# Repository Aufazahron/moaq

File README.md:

# 🛠️ Sensor Enclosure & Mechanical Components (Casing)

This repository contains a collection of 3D-printable enclosures and mechanical components designed for various sensor modules and mechanical systems. These parts were developed using **PTC Creo Parametric**.

## 📁 Project Structure

The project is organized into three main modules:

### 1. 🌊 Turbidity Sensor Enclosure (`/Turbidity`)
Designed to house and protect turbidity sensors used in water quality monitoring.
*   **Key Features:** Threaded assembly (ulir) for secure fit, sensor mounting base, and protective cover.
*   **Files:** Includes `.stl` for 3D printing and `.prt`/`.asm` for CAD modification.
*   **Visuals:**

### 2. 📏 Ultrasonic Sensor Casing (`/Ultrasonic_Casing`)
A custom mount and enclosure for HC-SR04 type ultrasonic sensors.
*   **Key Features:** Dual-bore front for sensor transducers, compact form factor, and mounting rails.
*   **Files:** `.stl` and `.prt`.
*   **Visuals:**

### 3. 🧪 Stirrer Handle (`/Gagang_Pengaduk`)
Mechanical component for manual or automated stirring systems.
*   **Key Features:** Ergonomic design/compatible connector for stirring rods.
*   **Files:** `.stl` and `.prt`.
*   **Visuals:**

## 🚀 Getting Started

### Prerequisites
*   **For Printing:** Any 3D slicer (Cura, PrusaSlicer, etc.) and a 3D printer.
*   **For Modification:** PTC Creo Parametric (Educational Edition or Professional).

### Installation / Usage
1.  Clone this repository to your local machine.
2.  Navigate to the desired folder.
3.  Use the `.stl` files directly for 3D printing.
4.  Use the `.prt` or `.asm` files if you need to adjust dimensions or features.

## 🛠️ Built With
*   **PTC Creo Parametric** - CAD Software used for modeling.
*   **STL Format** - Ready for 3D Printing.

---
*Developed for sensor integration and mechanical prototyping.*

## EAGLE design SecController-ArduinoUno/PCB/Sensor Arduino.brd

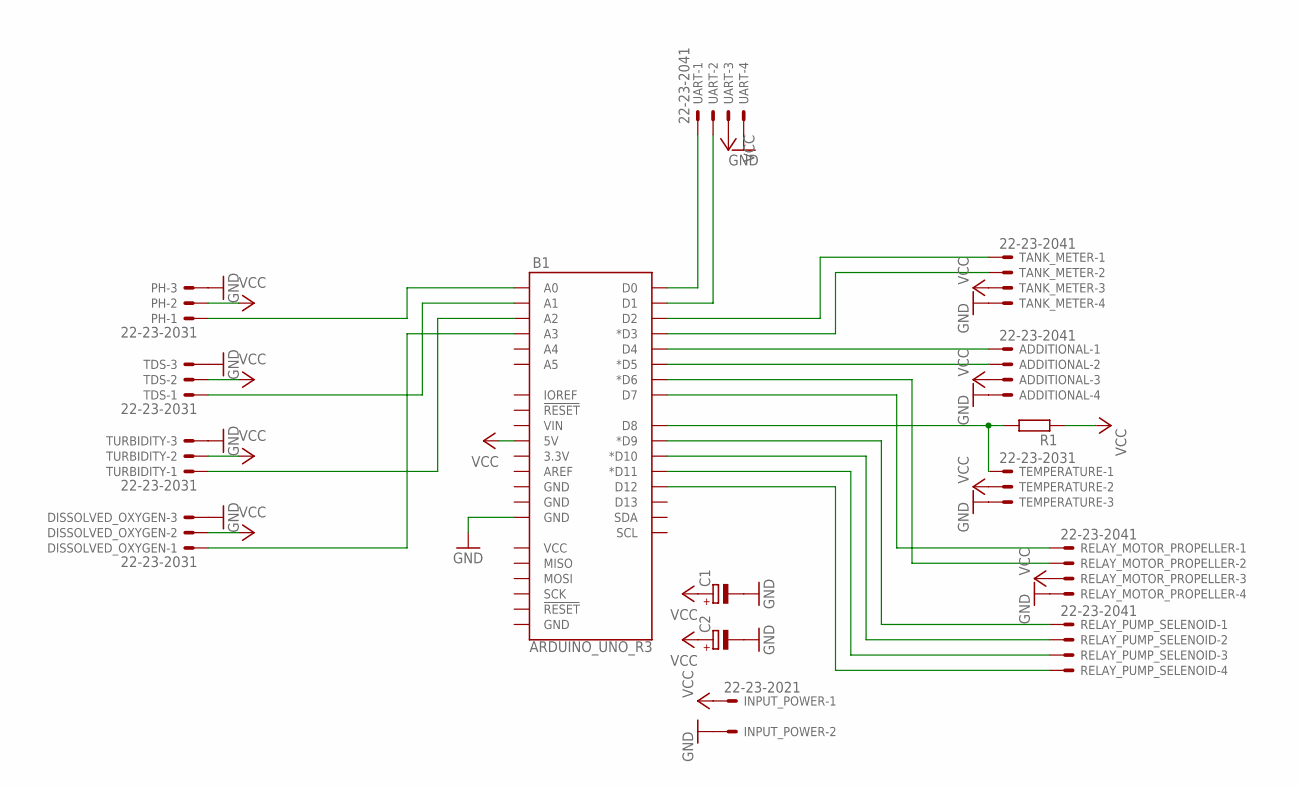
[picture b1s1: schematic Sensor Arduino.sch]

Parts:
ADDITIONAL: 22-23-2041
B1: ARDUINO_UNO_R3; ARDUINO_R3
C1: CPOL-EUE5-10.5; E5-10,5
C2: CPOL-EUE5-6; E5-6
DISSOLVED_OXYGEN: 22-23-2031
INPUT_POWER: 22-23-2021
PH: 22-23-2031
R1: R-EU_0207/12; 0207/12
RELAY_MOTOR_PROPELLER: 22-23-2041
RELAY_PUMP_SELENOID: 22-23-2041
TANK_METER: 22-23-2041
TDS: 22-23-2031
TEMPERATURE: 22-23-2031
TURBIDITY: 22-23-2031
UART: 22-23-2041

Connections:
GND: ADDITIONAL.4, B1.GND@2 (GND), C1.-, C2.-, DISSOLVED_OXYGEN.3, INPUT_POWER.2, PH.3, RELAY_MOTOR_PROPELLER.4, TANK_METER.4, TDS.3, TEMPERATURE.3, TURBIDITY.3, UART.4
unnamed: B1.A0, PH.1
unnamed: B1.A1, TDS.1
unnamed: B1.A2, TURBIDITY.1
unnamed: B1.A3, DISSOLVED_OXYGEN.1
unnamed: B1.D2, TANK_METER.1
unnamed: B1.D3 (*D3), TANK_METER.2
unnamed: ADDITIONAL.1, B1.D4
unnamed: ADDITIONAL.2, B1.D5 (*D5)
unnamed: B1.D8, R1.2, TEMPERATURE.1
unnamed: B1.D6 (*D6), RELAY_MOTOR_PROPELLER.2
unnamed: B1.D7, RELAY_MOTOR_PROPELLER.1
unnamed: B1.D9 (*D9), RELAY_PUMP_SELENOID.1
unnamed: B1.D10 (*D10), RELAY_PUMP_SELENOID.2
unnamed: B1.D11 (*D11), RELAY_PUMP_SELENOID.3
unnamed: B1.D12, RELAY_PUMP_SELENOID.4
unnamed: B1.D1, UART.2
unnamed: B1.D0, UART.1
VCC: ADDITIONAL.3, B1.5V, C1.+, C2.+, DISSOLVED_OXYGEN.2, INPUT_POWER.1, PH.2, R1.1, RELAY_MOTOR_PROPELLER.3, TANK_METER.3, TDS.2, TEMPERATURE.2, TURBIDITY.2, UART.3

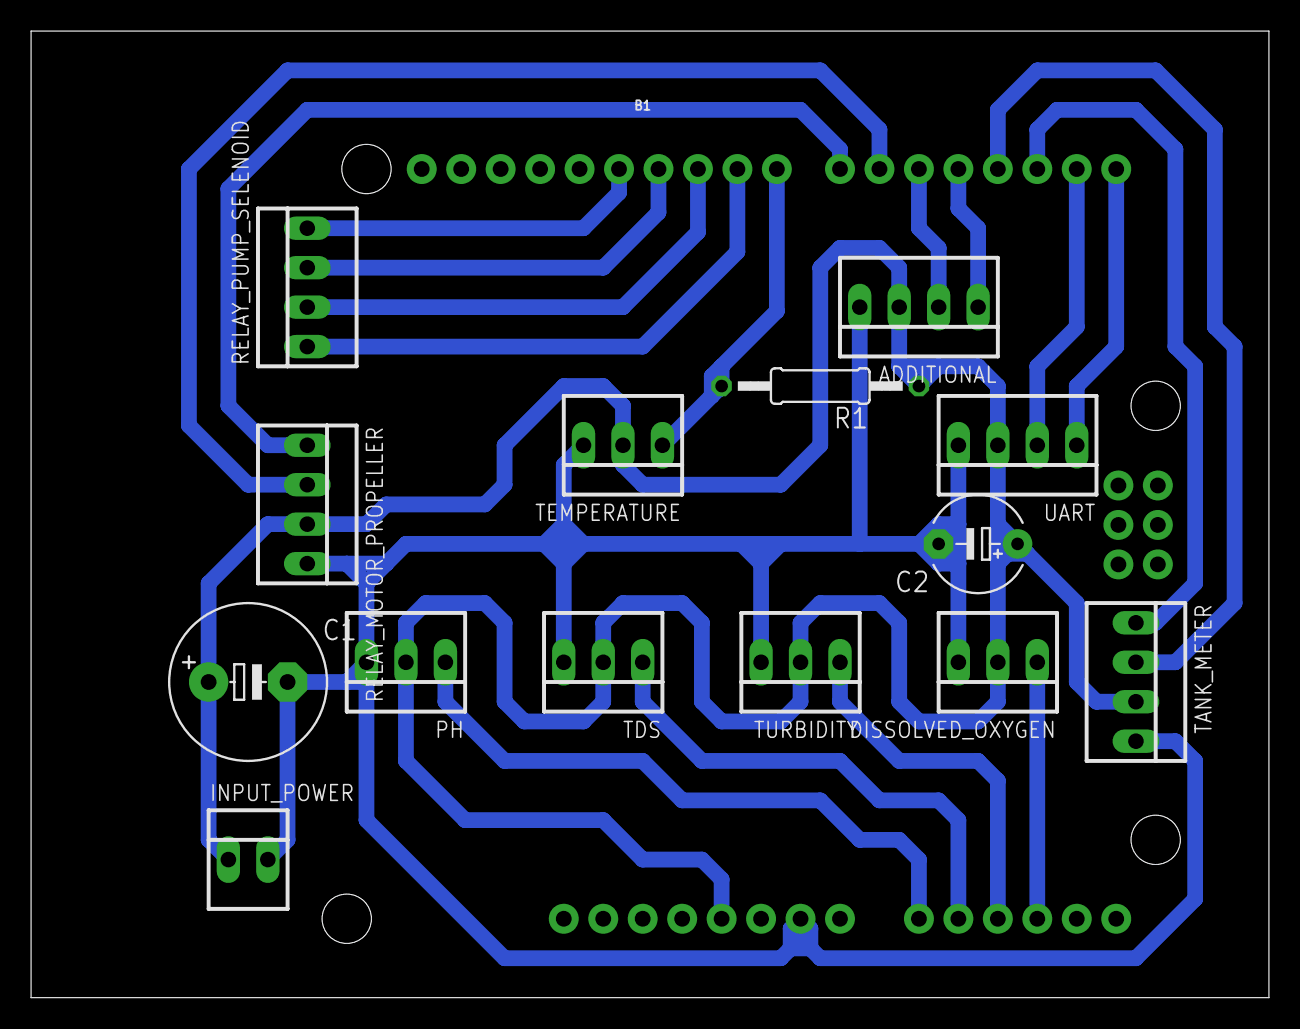
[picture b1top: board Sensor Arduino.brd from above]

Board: 2 copper layers, 79.7 x 62.2 mm, 15 parts (0 on the bottom side), 19 nets.

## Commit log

2026-01-05 Initial commit: Sistem Monitoring Air Kolam - Dashboard & API ready
2026-01-06 Update Viewer
2026-01-06 Upload Readme
2026-01-06 Initial commit for controller project: Smart Water Monitoring System
2026-01-06 Add sensor enclosures and mechanical components (casing)

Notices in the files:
parts and their libraries:
SparkFun-Boards: Licensing: Creative Commons ShareAlike 4.0 International - https://creativecommons.org/licenses/by-sa/4.0
